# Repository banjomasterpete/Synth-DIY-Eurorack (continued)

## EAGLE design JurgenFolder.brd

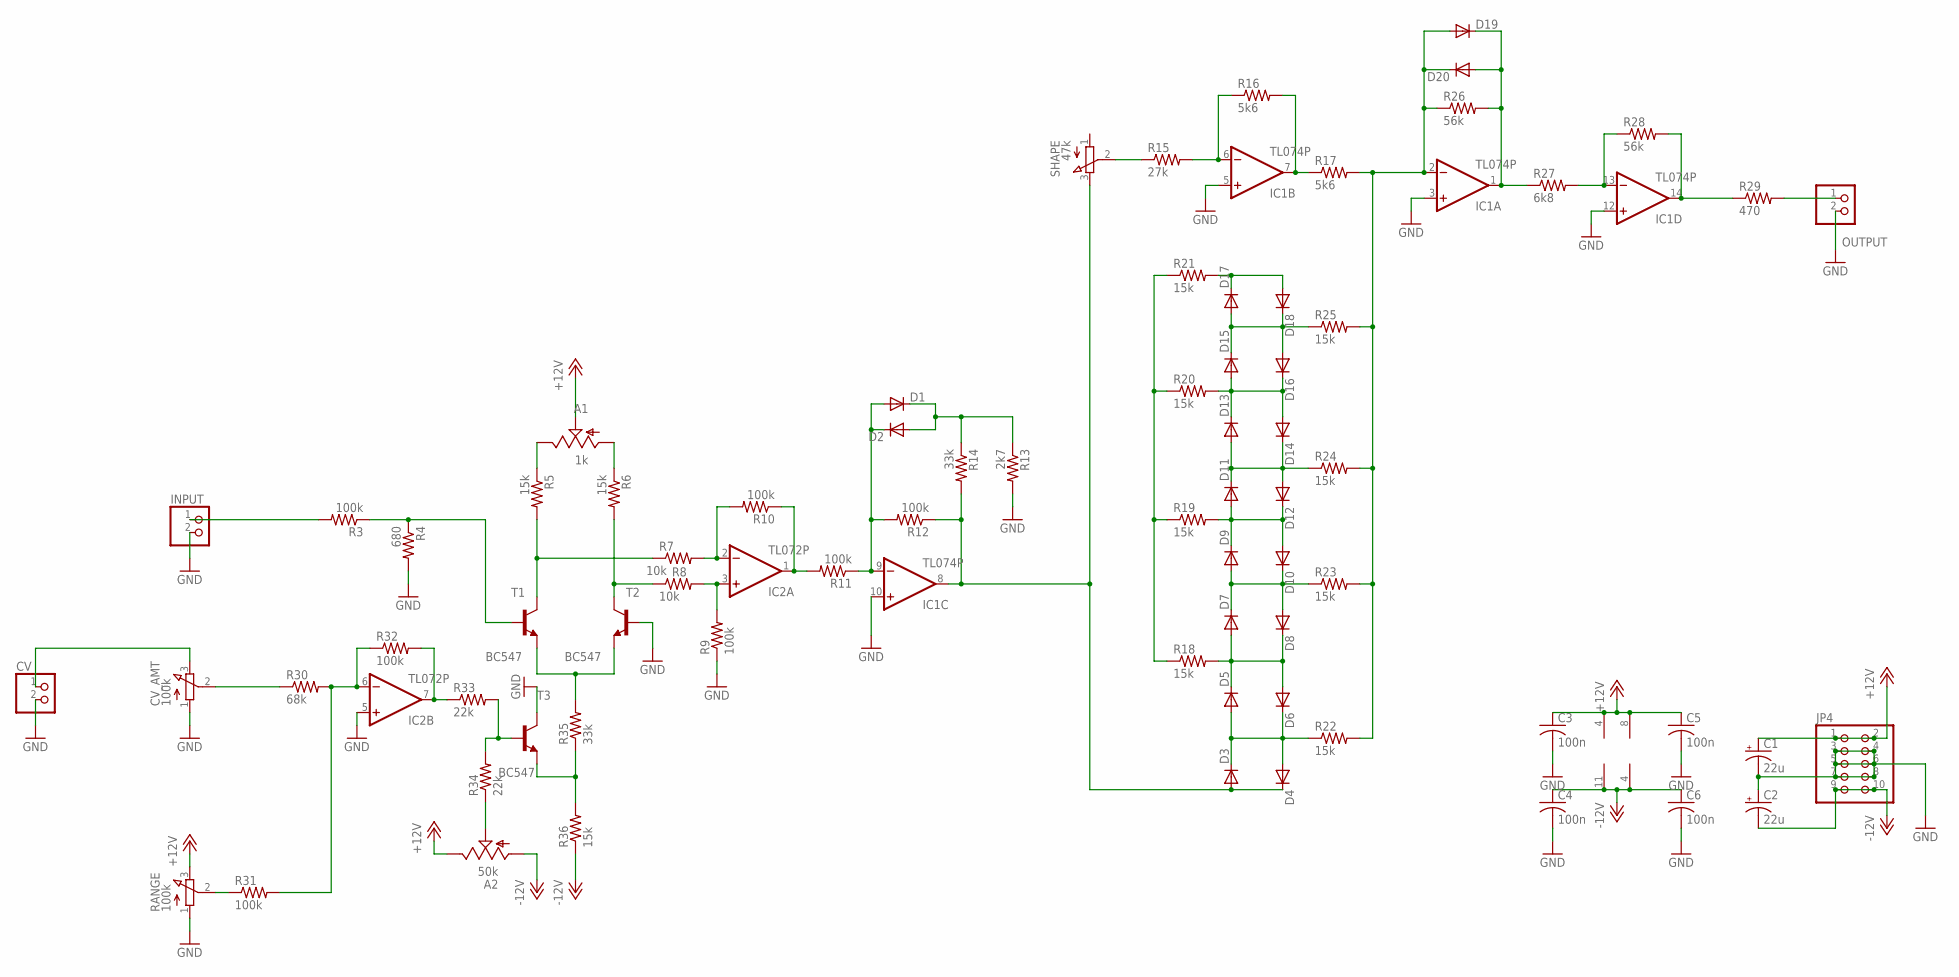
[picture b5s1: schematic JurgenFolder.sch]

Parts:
A1: 1k; S64W
A2: 50k; S64W
C1, C2: 22u; E3,5-8
C3, C4, C5, C6: 100n; C025-030X050
CV: PINHD-1X2; 1X02
CV_AMT: 100k; 3RP/1610N
D1, D2, D3, D4, D5, D6, D7, D8, D9, D10, D11, D12, D13, D14, D15, D16, D17, D18, D19, D20: 1N4148DO35-7; DO35-7
IC1: TL074P; DIL14
IC2: TL072P; DIL08
INPUT: PINHD-1X2; 1X02
JP4: PINHD-2X5; 2X05
OUTPUT: PINHD-1X2; 1X02
R3, R9, R10, R11, R12, R31, R32: 100k; 0204/7
R4: 680; 0204/7
R5, R6, R18, R19, R20, R21, R22, R23, R24, R25, R36: 15k; 0204/7
R7, R8: 10k; 0204/7
R13: 2k7; 0204/7
R14, R35: 33k; 0204/7
R15: 27k; 0204/7
R16, R17: 5k6; 0204/7
R26, R28: 56k; 0204/7
R27: 6k8; 0204/7
R29: 470; 0204/7
R30: 68k; 0204/7
R33, R34: 22k; 0204/7
RANGE: 100k; 3RP/1610N
SHAPE: 47k; 3RP/1610N
T1, T2, T3: BC547; TO92

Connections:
+12V: A1.S, A2.E, C1.+, C3.1, C5.1, IC1.4 (V+), IC2.8 (V+), JP4.1, JP4.2, RANGE.3 (E)
-12V: A2.A, C2.-, C4.1, C6.1, IC1.11 (V-), IC2.4 (V-), JP4.9, JP4.10, R36.1
GND: C1.-, C2.+, C3.2, C4.2, C5.2, C6.2, CV.2, CV_AMT.1 (A), IC1.3 (+IN), IC1.5 (+IN), IC1.10 (+IN), IC1.12 (+IN), IC2.5 (+IN), INPUT.2, JP4.3, JP4.4, JP4.5, JP4.6, JP4.7, JP4.8, OUTPUT.2, R4.2, R9.1, R13.2, RANGE.1 (A), T2.2 (B), T3.3 (C)
unnamed: INPUT.1, R3.2
unnamed: R3.1, R4.1, T1.2 (B)
unnamed: IC2.2 (-IN), R7.2, R10.2
unnamed: R5.2, R7.1, T1.3 (C)
unnamed: A1.E, R5.1
unnamed: A1.A, R6.1
unnamed: R6.2, R8.1, T2.3 (C)
unnamed: R35.2, T1.1 (E), T2.1 (E)
unnamed: IC2.3 (+IN), R8.2, R9.2
unnamed: D3.A, D4.C, IC1.8 (OUT), R12.1, R14.2, SHAPE.3 (E)
unnamed: IC2.1 (OUT), R10.1, R11.2
unnamed: D1.A, D2.C, IC1.9 (-IN), R11.1, R12.2
unnamed: R15.1, SHAPE.2 (S)
unnamed: D13.C, D14.A, D15.A, D16.C, R20.2
unnamed: D1.C, D2.A, R13.1, R14.1
unnamed: IC2.6 (-IN), R30.2, R31.2, R32.1
unnamed: CV_AMT.2 (S), R30.1
unnamed: IC1.6 (-IN), R15.2, R16.1
unnamed: IC2.7 (OUT), R32.2, R33.1
unnamed: R31.1, RANGE.2 (S)
unnamed: A2.S, R34.1
unnamed: R33.2, R34.2, T3.2 (B)
unnamed: R35.1, R36.2, T3.1 (E)
unnamed: OUTPUT.1, R29.2
unnamed: IC1.7 (OUT), R16.2, R17.1
unnamed: D19.A, D20.C, IC1.2 (-IN), R17.2, R22.2, R23.2, R24.2, R25.2, R26.1
unnamed: D19.C, D20.A, IC1.1 (OUT), R26.2, R27.1
unnamed: D15.C, D16.A, D17.A, D18.C, R25.1
unnamed: D11.C, D12.A, D13.A, D14.C, R24.1
unnamed: D9.C, D10.A, D11.A, D12.C, R19.2
unnamed: D7.C, D8.A, D9.A, D10.C, R23.1
unnamed: D5.C, D6.A, D7.A, D8.C, R18.2
unnamed: D3.C, D4.A, D5.A, D6.C, R22.1
unnamed: D17.C, D18.A, R21.2
unnamed: IC1.13 (-IN), R27.2, R28.1
unnamed: R18.1, R19.1, R20.1, R21.1
unnamed: CV.1, CV_AMT.3 (E)
unnamed: IC1.14 (OUT), R28.2, R29.1

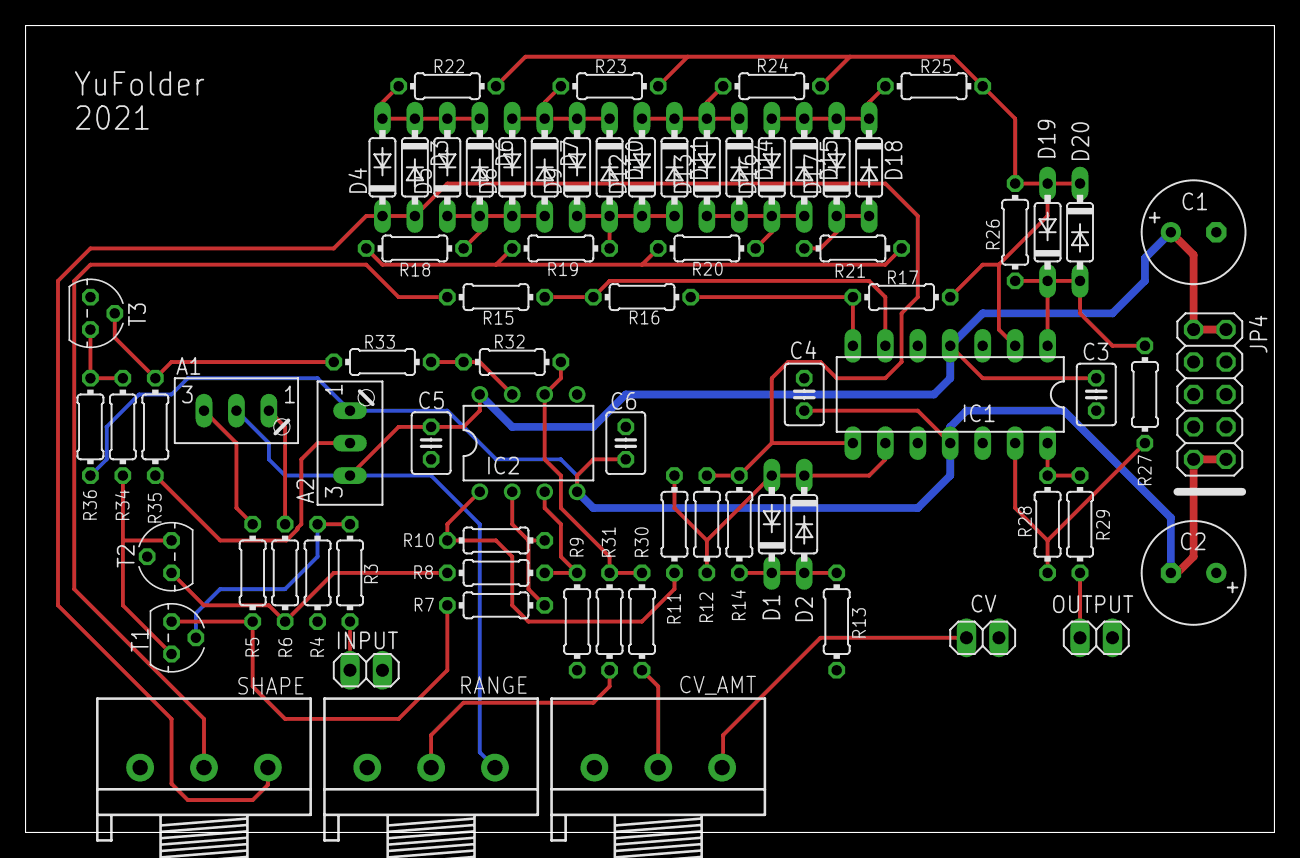
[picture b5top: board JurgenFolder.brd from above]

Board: 2 copper layers, 97.8 x 63.2 mm, 74 parts (0 on the bottom side), 41 nets.

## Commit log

2021-04-17 Create YuFolder Docs
2021-12-09 Add files via upload
    This knob should fit pretty much any shaft type. The side hole is sized for #4-40 heat set inserts from McMaster Carr
    Inserts PN: 93365A120
    Set screws PN: 94355A130
2023-09-10 6HP Precision Mult & Adder
    This is a multiple/ adder utility that is precise enough to use for v/oct signals.
    2x 1 to 3 buffered mults (channel 2 normals to 1)
    2x 3 to 1 buffered adders
2023-09-15 Add files via upload
    Added schematic pdf
2024-02-21 Create DPG (voltage-controlled distortion) - kicad
2024-02-21 Create VCD
